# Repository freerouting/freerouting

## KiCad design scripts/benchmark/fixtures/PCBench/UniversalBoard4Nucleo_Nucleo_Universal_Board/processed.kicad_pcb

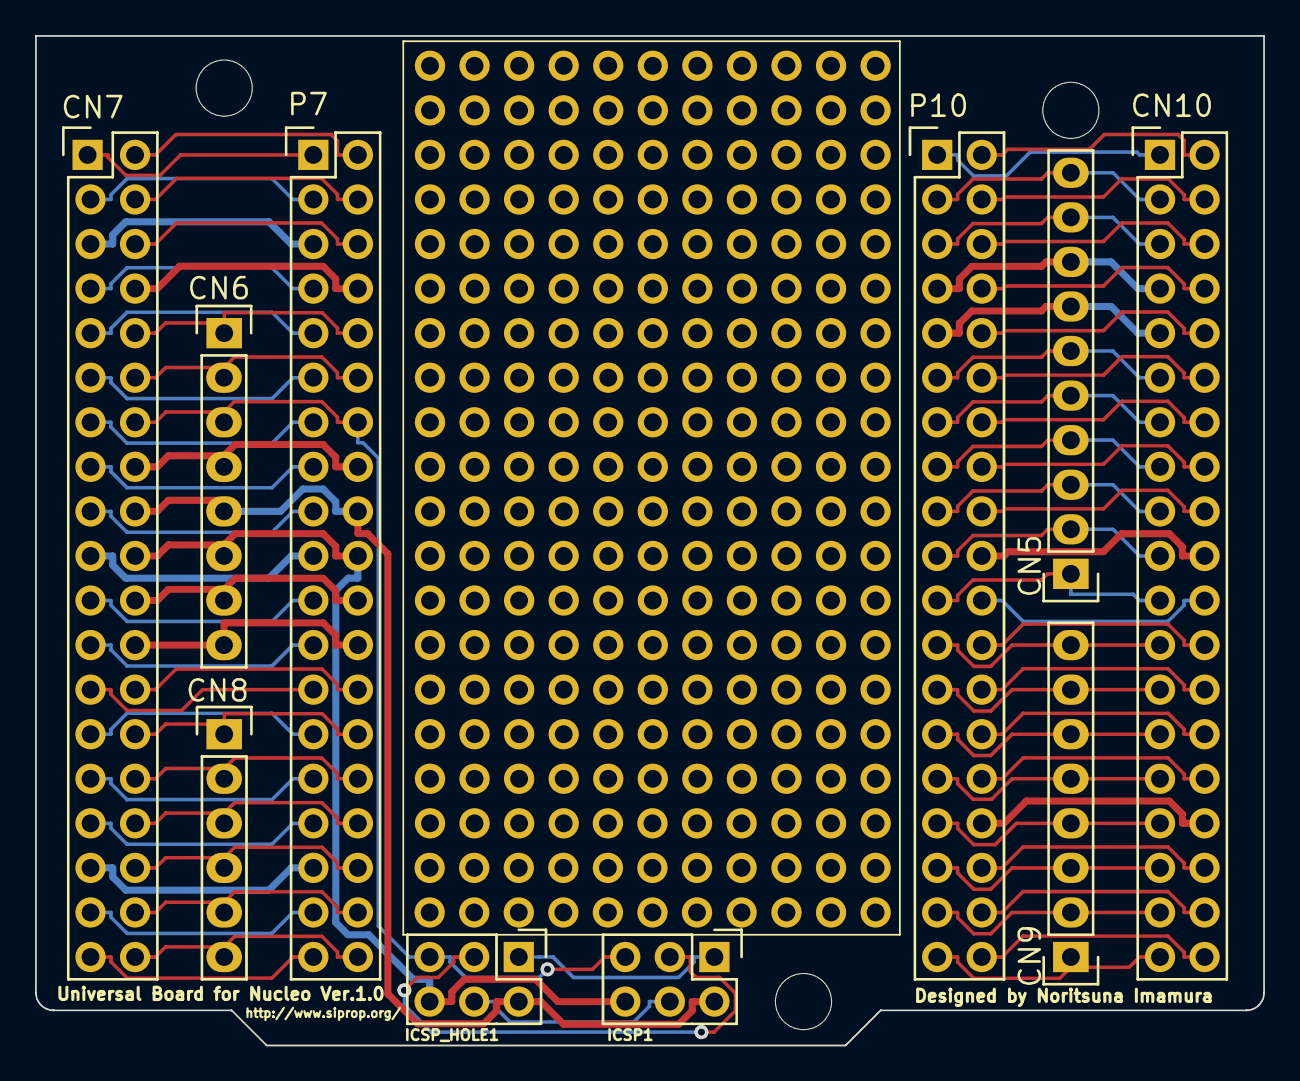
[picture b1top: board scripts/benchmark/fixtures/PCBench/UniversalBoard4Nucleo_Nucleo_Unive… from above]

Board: 2 copper layers, 70.0 x 57.5 mm, 68 parts (0 on the bottom side), 79 nets.

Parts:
CN5: CONN_01X10; Pin_Header_Straight_1x10
CN6, CN9: CONN_01X08; Pin_Header_Straight_1x08
CN7, CN10: CONN_02X19; Pin_Header_Straight_2x19
CN8: CONN_01X06; Pin_Header_Straight_1x06
H1, H2, H3, H4, H5, H6, H7, H8, H9, H10, H11, H12, H13, H14, H15, H16, H17, H18, H19, H20, H21, H22, H23, H24, H25, H26, H27, H28, H29, H30, H31, H32, H33, H34, H35, H36, H37, H38, H39, H40, H41, H42, H43, H44, H45, H46, H47, H48, H49, H50, H51, H52, H56, H57, H58: WirePads_Straight_1x04; Wire_Pad_Straight_1x04
ICSP1: CONN_02X03; Pin_Header_Straight_2x03
ICSP_HOLE1: HOLE_02X03; Pin_Header_Straight_2x03
MH1, MH2, MH3: MountingHole_3.2mm_M3
P7, P10: HOLE_02X19; Pin_Header_Straight_2x19

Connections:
/PA1: CN7.1, P7.1
/PA2: CN7.2, P7.2
/PA3: CN7.3, P7.3
/PA4: CN7.4, P7.4
/PA5: CN7.5, P7.5
/PA6: CN7.6, P7.6
/PA7: CN7.7, P7.7
/PA8: CN7.8, P7.8
/PA9: CN7.9, P7.9
/PA10: CN6.1, CN7.10, P7.10
/PA11: CN7.11, P7.11
/PA12: CN6.2, CN7.12, P7.12
/PA13: CN7.13, P7.13
/PA14: CN6.3, CN7.14, ICSP1.5, ICSP_HOLE1.5, P7.14
/PA15: CN7.15, P7.15
/PA16: CN6.4, CN7.16, P7.16
/PA17: CN7.17, P7.17
/PA18: CN6.5, CN7.18, ICSP1.2, ICSP_HOLE1.2, P7.18
/PA19: CN7.19, P7.19
/PA20: CN6.6, CN7.20, ICSP1.6, ICSP_HOLE1.6, P7.20
/PA21: CN7.21, P7.21
/PA22: CN6.7, CN7.22, P7.22
/PA23: CN7.23, P7.23
/PA24: CN6.8, CN7.24, P7.24
/PA25: CN7.25, P7.25
/PA26: CN7.26, P7.26
/PA27: CN7.27, P7.27
/PA28: CN7.28, CN8.1, P7.28
/PA29: CN7.29, P7.29
/PA30: CN7.30, CN8.2, P7.30
/PA31: CN7.31, P7.31
/PA32: CN7.32, CN8.3, P7.32
/PA33: CN7.33, P7.33
/PA34: CN7.34, CN8.4, P7.34
/PA35: CN7.35, P7.35
/PA36: CN7.36, CN8.5, P7.36
/PA37: CN7.37, P7.37
/PA38: CN7.38, CN8.6, P7.38
/PB1: CN10.1, P10.1
/PB2: CN10.2, P10.2
/PB3: CN5.10, CN10.3, P10.3
/PB4: CN10.4, P10.4
/PB5: CN5.9, CN10.5, P10.5
/PB6: CN10.6, P10.6
/PB7: CN5.8, CN10.7, P10.7
/PB8: CN10.8, P10.8
/PB9: CN5.7, CN10.9, P10.9
/PB10: CN10.10, P10.10
/PB11: CN5.6, CN10.11, P10.11
/PB12: CN10.12, P10.12
/PB13: CN5.5, CN10.13, P10.13
/PB14: CN10.14, P10.14
/PB15: CN5.4, CN10.15, P10.15
/PB16: CN10.16, P10.16
/PB17: CN5.3, CN10.17, P10.17
/PB18: CN10.18, P10.18
/PB19: CN5.2, CN10.19, P10.19
/PB20: CN10.20, P10.20
/PB21: CN5.1, CN10.21, P10.21
/PB22: CN10.22, P10.22
/PB23: CN9.8, CN10.23, P10.23
/PB24: CN10.24, P10.24
/PB25: CN9.7, CN10.25, P10.25
/PB26: CN10.26, P10.26
/PB27: CN9.6, CN10.27, P10.27
/PB28: CN10.28, P10.28
/PB29: CN9.5, CN10.29, P10.29
/PB30: CN10.30, P10.30
/PB31: CN9.4, CN10.31, P10.31
/PB32: CN10.32, P10.32
/PB33: CN9.3, CN10.33, P10.33
/PB34: CN10.34, P10.34
/PB35: CN9.2, CN10.35, P10.35
/PB36: CN10.36, P10.36
/PB37: CN9.1, CN10.37, P10.37
/PB38: CN10.38, P10.38
/PC1: ICSP1.1, ICSP_HOLE1.1
/PC3: ICSP1.3, ICSP_HOLE1.3
/PC4: ICSP1.4, ICSP_HOLE1.4

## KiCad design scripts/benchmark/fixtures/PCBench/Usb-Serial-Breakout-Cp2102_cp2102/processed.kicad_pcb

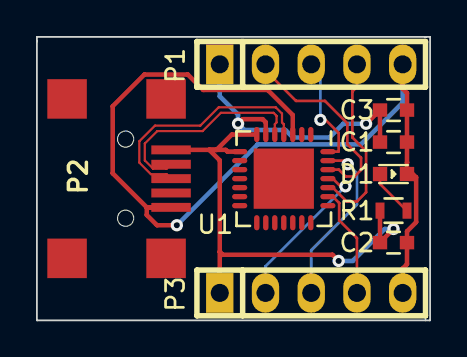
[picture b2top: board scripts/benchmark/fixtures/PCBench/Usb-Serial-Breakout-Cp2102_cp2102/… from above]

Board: 2 copper layers, 21.8 x 15.7 mm, 10 parts (1 on the bottom side), 12 nets.

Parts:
C1: 10uf; CAP_0603
C2: 1uf; CAP_0603
C3: 0.1uf; CAP_0603
D1: LED; LED-0603
LOGO1: LEMBED-LOGO; LOGO_LEMBED
P1, P3: CONN_01X05; PIN_SOCKET_5
P2: MICRO-USB-B; USB_B_MINI_SMD
R1: 330; R_0603
U1: CP2102; QFN-28-1EP_5x5mm_Pitch0.5mm

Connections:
+3V3: C1.1, C3.1, P1.1, U1.6
/CTS: P3.4, U1.23
/D+: P2.3, U1.4
/D-: P2.2, U1.5
/DSR: P3.3, U1.27
/DTR: P1.3, U1.28
/RTS: P1.4, U1.24
/RXD: P3.2, U1.25
/TXD: P1.2, U1.26
GND: C1.2, C2.2, C3.2, D1.2, P1.5, P2.5, P3.5, U1.3
unnamed: D1.1, R1.2
VCC: C2.1, P2.1, P3.1, R1.1, U1.7, U1.8

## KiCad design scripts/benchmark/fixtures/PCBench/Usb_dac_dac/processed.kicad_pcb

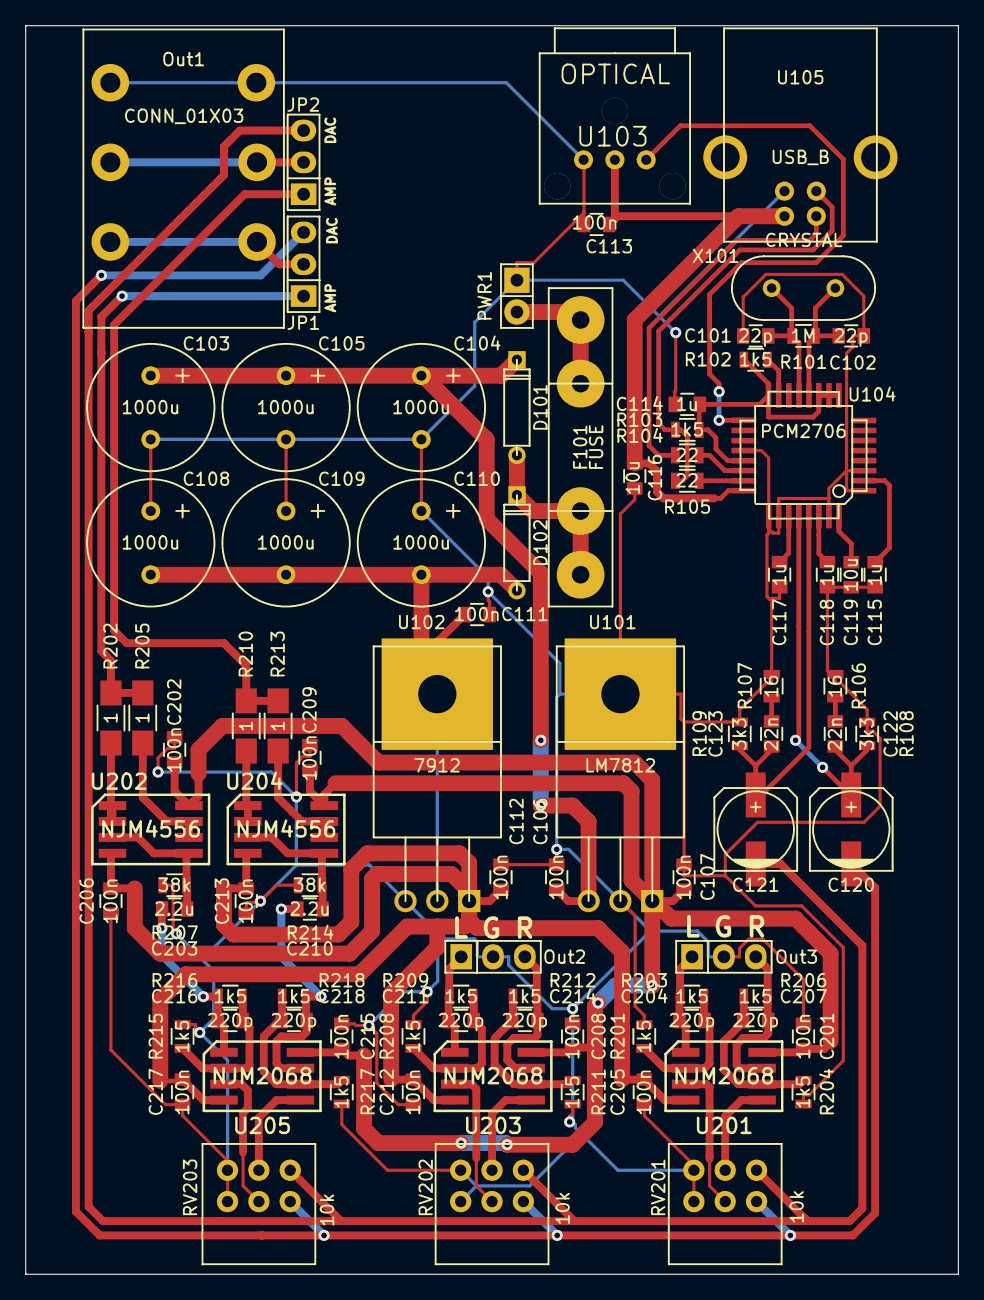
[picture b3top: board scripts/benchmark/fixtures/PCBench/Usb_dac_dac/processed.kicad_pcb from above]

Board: 2 copper layers, 74.4 x 99.6 mm, 91 parts (0 on the bottom side), 55 nets.

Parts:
C101, C102: 22p; C_0805
C103, C104, C105, C108, C109, C110: 1000u; Elko_vert_20x10mm_RM5
C106, C107, C111, C112, C113, C201, C202, C205, C206, C208, C209, C212, C213, C215, C217: 100n; C_0805
C114, C115, C117, C118: 1u; C_0805
C116, C119: 10u; C_0805
C120, C121: 100u; c_elec_6.3x5.3
C122, C123: 22n; C_0805
C203, C210: 2.2u; C_0805
C204, C207, C211, C214, C216, C218: 220p; C_0805
D101, D102: DIODE; D3
F101: FUSE; FUSE5-20
JP1, JP2: CONN_01X03; Pin_Header_Straight_1x03
Out1: CONN_01X03; SIKA
Out2, Out3: CONN_01X03; Pin_Header_Straight_1x03
PWR1: CONN_01X02; Pin_Header_Straight_1x02
R101: 1M; R_0805
R102, R103, R201, R203, R204, R206, R208, R209, R211, R212, R215, R216, R217, R218: 1k5; R_0805
R104, R105: 22; R_0805
R106, R107: 16; R_0805
R108, R109: 3k3; R_0805
R202, R205, R210, R213: 1; R_1206_HandSoldering
R207, R214: 38k; R_0805
RV201, RV202, RV203: 10k; RK097
U101: LM7812; TO220
U102: 7912; TO220
U103: OPTICAL; KFOX
U104: PCM2706; TQFP-32
U105: USB_B
U201, U203, U205: NJM2068; SOIC 8
U202, U204: NJM4556; SOIC 8
X101: CRYSTAL; HC-49V

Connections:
3V3: C114.2, R102.2, R103.2, U104.9, U104.10, U104.11, U104.16, U104.21
+5V: C113.2, C116.1, U103.2, U104.24, U105.1
+12V: C107.1, C201.2, C202.2, C208.2, C209.2, C215.2, U101.3, U201.8, U202.8, U203.8, U204.8, U205.8
-12V: C112.2, C205.2, C206.2, C212.2, C213.2, C217.2, U102.3, U201.4, U202.4, U203.4, U204.4, U205.4
/Buffers/Left out 1: JP1.1, R202.2, R205.2
/Buffers/Left out 2: C211.2, Out2.1, R209.2, U203.1
/Buffers/Left out 3: C204.2, Out3.1, R203.2, U201.1
/Buffers/Left_in: C120.2, JP1.3, RV201.3, RV202.3, RV203.3
/Buffers/Right out 1: JP2.1, R210.2, R213.2
/Buffers/Right out 2: C214.2, Out2.3, R212.2, U203.7
/Buffers/Right out 3: C207.2, Out3.3, R206.2, U201.7
/Buffers/Right_in: C121.2, JP2.3, RV201.6, RV202.6, RV203.6
AGND: C101.2, C102.2, C103.2, C104.2, C105.2, C106.2, C107.2, C108.1, C109.1, C110.1, C111.1, C112.1, C113.1, C114.1, C115.2, C116.2, C117.2, C118.2, C119.2, C201.1, C202.1, C205.1, C206.1, C208.1, C209.1, C212.1, C213.1, C215.1, C217.1, Out1.1, Out2.2, Out3.2, PWR1.1, R106.2, R107.2, R108.2, R109.2, R201.2, R204.2, R207.2, R208.2, R211.2, R214.2, R215.2, R217.2, RV201.1, RV201.4, RV202.1, RV202.4, RV203.1, RV203.4, U101.2, U102.1, U103.1, U104.1, U104.3, U104.20, U104.25, U104.26, U104.31, U105.4
unnamed: C101.1, R101.2, U104.13, X101.2
unnamed: C102.1, R101.1, U104.12, X101.1
unnamed: C103.1, C104.1, C105.1, C106.1, D101.2, U101.1
unnamed: C108.2, C109.2, C110.2, C111.2, D102.1, U102.2
unnamed: C115.1, U104.2
unnamed: C117.1, U104.27
unnamed: C118.1, U104.30
unnamed: C119.1, U104.32
unnamed: C120.1, C122.1, R108.1, U104.28
unnamed: C121.1, C123.1, R109.1, U104.29
unnamed: C122.2, R106.1
unnamed: C123.2, R107.1
unnamed: C203.1, C216.2, R216.2, U205.1
unnamed: C203.2, R207.1, U202.3, U202.5
unnamed: C204.1, R201.1, R203.1, U201.2
unnamed: C207.1, R204.1, R206.1, U201.6
unnamed: C210.1, C218.2, R218.2, U205.7
unnamed: C210.2, R214.1, U204.3, U204.5
unnamed: C211.1, R208.1, R209.1, U203.2
unnamed: C214.1, R211.1, R212.1, U203.6
unnamed: C216.1, R215.1, R216.1, U205.2
unnamed: C218.1, R217.1, R218.1, U205.6
unnamed: D101.1, D102.2, F101.2
unnamed: F101.1, PWR1.2
unnamed: JP1.2, Out1.3
unnamed: JP2.2, Out1.2
unnamed: R102.1, U104.15
unnamed: R103.1, R105.2, U105.3
unnamed: R104.1, U104.22
unnamed: R104.2, U105.2
unnamed: R105.1, U104.23
unnamed: R202.1, U202.1, U202.2
unnamed: R205.1, U202.6, U202.7
unnamed: R210.1, U204.1, U204.2
unnamed: R213.1, U204.6, U204.7
unnamed: RV201.2, U201.3
unnamed: RV201.5, U201.5
unnamed: RV202.2, U203.3
unnamed: RV202.5, U203.5
unnamed: RV203.2, U205.3
unnamed: RV203.5, U205.5
unnamed: U103.3, U104.17
